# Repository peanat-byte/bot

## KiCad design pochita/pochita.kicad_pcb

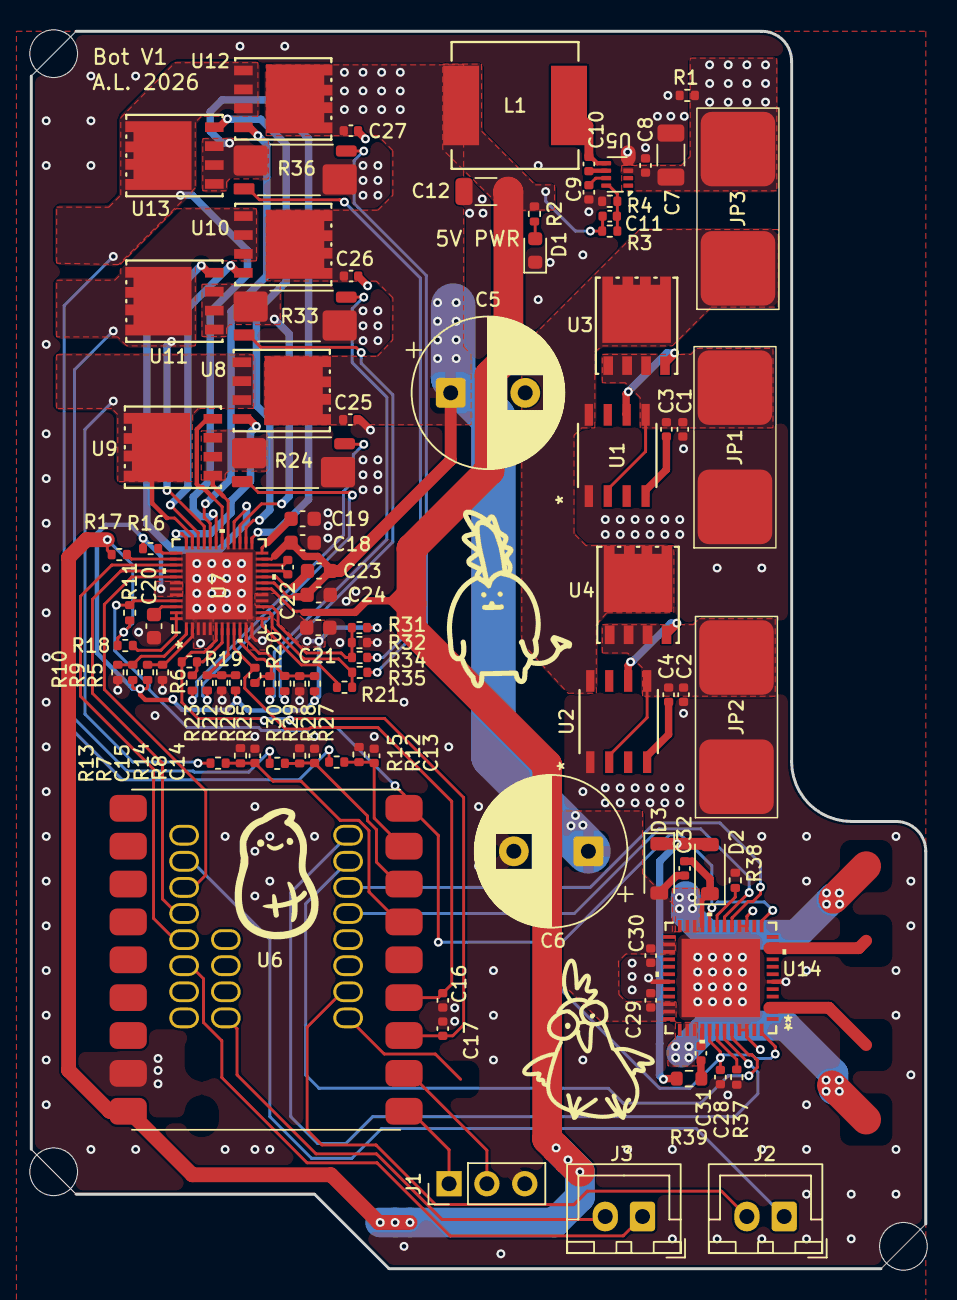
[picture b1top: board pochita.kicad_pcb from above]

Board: 4 copper layers, 60.0 x 83.0 mm, 98 parts (0 on the bottom side), 80 nets.

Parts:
C1, C2, C3, C4, C8, C9, C10, C11, C13, C14, C15, C16, C17, C22, C25, C26, C27, C28, C29, C30, C31, C32: C_0402_1005Metric
C5, C6: CP_Radial_D10.0mm_P5.00mm
C7, C12: C_1206_3216Metric
C18, C19, C20, C21, C23, C24: C_0603_1608Metric
D1: D_0603_1608Metric
D2, D3: D_SOD-123
H1, H2, H3: MountingHole_3.2mm_M3
J1: PinHeader_1x03_P2.54mm_Vertical
J2, J3: JST_XH_B2B-XH-A_1x02_P2.50mm_Vertical
JP1, JP2, JP3: 2-Pad
L1: IND_IHLP-3232DZ_VIS
R1, R2, R3, R4, R5, R6, R7, R8, R9, R10, R11, R12, R13, R14, R15, R16, R17, R18, R19, R20, R21, R22, R23, R25, R26, R27, R28, R29, R30, R31, R32, R34, R35, R37, R38: R_0402_1005Metric
R24, R33, R36: R_Shunt_Vishay_WSK2512_6332Metric_T1.19mm
R39: R_0603_1608Metric
U1, U2: SOIC8_D_TEX
U3, U4, U8, U9, U10, U11, U12, U13: SON_STL160N4F7_STM
U5: SOT-583-8
U6: ESP32-S3_Super_Mini
U7: VFQFPN48_ 6X6X1_STM
U14: VFQFPN48_7P15X7P15X0P5_STM

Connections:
+5V: C11.1, C12.1, L1.2, R2.1, R3.1, R11.1, R17.1, R18.1, U6.18 (5V), U7.18 (REGIN_3V3)
/Blade Motor/I1: C17.1, R19.1, U6.3 (GP1), U7.6 (OA_O1)
/Blade Motor/I2: C16.1, R20.1, U6.4 (GP2), U7.9 (OA_O2)
/Blade Motor/I3: R21.1, U7.13 (OA_O3)
/Blade Motor/IN1: U6.21 (GP16), U7.41 (INH1/IN1)
/Blade Motor/IN1N: R19.2, R23.1, U7.7 (OA_IN1N)
/Blade Motor/IN1P: R22.1, R25.1, R26.2, U7.8 (OA_IN1P)
/Blade Motor/IN2: U6.22 (GP17), U7.40 (INH2/IN2)
/Blade Motor/IN2N: R20.2, R30.1, U7.10 (OA_IN2N)
/Blade Motor/IN2P: R27.1, R28.2, R29.1, U7.11 (OA_IN2P)
/Blade Motor/IN3: U6.23 (GP18), U7.39 (INH3/IN3)
/Blade Motor/IN3N: R21.2, R35.1, U7.14 (OA_IN3N)
/Blade Motor/IN3P: R31.1, R32.2, R34.1, U7.15 (OA_IN3P)
/Blade Motor/V1: C15.1, R7.2, R13.1, U6.6 (GP4)
/Blade Motor/V2: C14.1, R8.2, R14.1, U6.7 (GP5)
/Blade Motor/V3: C13.1, R12.2, R15.1, U6.8 (GP6)
/Blade Motor/blade_motor_A: R13.2, U7.35 (OUT1), U8.1 (S), U8.2 (S), U8.3 (S), U9.5 (D)
/Blade Motor/blade_motor_B: R14.2, U7.33 (OUT2), U10.1 (S), U10.2 (S), U10.3 (S), U11.5 (D)
/Blade Motor/blade_motor_C: R15.2, U7.31 (OUT3), U12.1 (S), U12.2 (S), U12.3 (S), U13.5 (D)
/Blade Motor/nRST: C28.1, R11.2, U6.9 (GP7), U7.45 (NSTBY), U14.13 (OCDB), U14.20 (ENB), U14.41 (ENA), U14.48 (OCDA)
/Drive Motors/INA1: U6.31 (GP39), U14.43 (IN1A)
/Drive Motors/INA2: U6.32 (GP40), U14.44 (IN2A)
/Drive Motors/INB1: U6.33 (GP41), U14.17 (IN1B)
/Drive Motors/INB2: U6.34 (GP42), U14.18 (IN2B)
/Drive Motors/drive_motor_A1: U14.2 (OUT1A), U14.3 (OUT1A)
/Drive Motors/drive_motor_A2: U14.38 (OUT2A), U14.39 (OUT2A)
/Drive Motors/drive_motor_B1: U14.10 (OUT1B), U14.11 (OUT1B)
/Drive Motors/drive_motor_B2: U14.22 (OUT2B), U14.23 (OUT2B)
GND: C1.2, C2.2, C5.2, C6.2, C7.2, C8.2, C9.2, C12.2, C13.2, C14.2, C15.2, C16.2, C17.2, C18.2, C19.2, C20.2, C21.2, C24.2, C25.2, C26.2, C27.2, C28.2, C29.2, C30.2, D1.1 (K), J1.3, JP1.1 (A), JP2.1 (A), R1.2, R4.2, R6.2, R7.1, R8.1, R10.2, R12.1, R24.4, R26.1, R28.1, R32.1, R33.4, R36.4, R37.2, R38.2, U1.1 (GND), U2.1 (GND), U5.4 (GND), U6.17 (GND), U7.3 (C_IN1), U7.4 (C_IN2), U7.5 (C_IN3), U7.12 (AGND), U7.49 (EPAD), U14.6 (GND), U14.15 (SENSEB), U14.16 (SENSEB), U14.31 (GND), U14.45 (SENSEA), U14.46 (SENSEA), U14.49 (EPAD)
unnamed: C31.2, R39.1
unnamed: D1.2 (A), R2.2
unnamed: D2.1 (K), D3.2 (A), R39.2
unnamed: C32.2, D3.1 (K), U14.21 (VBOOT)
unnamed: J1.1, U6.1 (TX)
unnamed: J1.2, U6.2 (RX)
unnamed: J2.1, U6.20 (GP15)
unnamed: J2.2, U6.37 (GP47)
unnamed: J3.1, U6.24 (GP21)
unnamed: J3.2, U6.30 (GP38)
unnamed: JP3.1 (A), U1.8 (CATHODE), U2.8 (CATHODE), U3.5 (D), U4.5 (D)
unnamed: R22.2, R24.2
unnamed: R23.2, R24.3
unnamed: R29.2, R33.2
unnamed: R30.2, R33.3
unnamed: R34.2, R36.2
unnamed: R35.2, R36.3
unnamed: U1.6 (GATE), U3.4 (G)
unnamed: C3.2, U1.4 (VCAP)
unnamed: U2.6 (GATE), U4.4 (G)
unnamed: C4.2, U2.4 (VCAP)
unnamed: C10.1, U5.6 (BST)
unnamed: C11.2, R3.2, R4.1, U5.8 (FB)
unnamed: C9.1, U5.7 (SS)
unnamed: C10.2, L1.1, U5.5 (SW)
unnamed: R18.2, U7.47 (EN), U7.48 (NFAULT)
unnamed: R16.2, U7.37 (FLAG)
unnamed: U7.36 (GHS1), U8.4 (G)
unnamed: U7.30 (GLS1), U9.4 (G)
unnamed: R5.2, R6.1, U7.2 (IGATE)
unnamed: C20.1, U7.46 (LGC_CAP)
unnamed: C22.1, U7.22 (NCAP)
unnamed: C22.2, U7.21 (PCAP)
unnamed: R24.1, U7.29 (SLS1), U9.1 (S), U9.2 (S), U9.3 (S)
unnamed: R33.1, U7.27 (SLS2), U11.1 (S), U11.2 (S), U11.3 (S)
unnamed: R36.1, U7.25 (SLS3), U13.1 (S), U13.2 (S), U13.3 (S)
unnamed: R9.2, R10.1, U7.1 (TCC)
unnamed: C23.1, U7.20 (VBOOT)
unnamed: C19.1, U7.24 (VCC)
unnamed: R17.2, U7.38 (VDSTH)
unnamed: U7.34 (GHS2), U10.4 (G)
unnamed: U7.28 (GLS2), U11.4 (G)
unnamed: U7.32 (GHS3), U12.4 (G)
unnamed: U7.26 (GLS3), U13.4 (G)
unnamed: R37.1, U14.42 (PROGCLA)
unnamed: R38.1, U14.19 (PROGCLB)
unnamed: C31.1, U14.40 (VCP)
VBAT: C1.1, C3.1, JP1.2 (B), U1.2 (EN), U1.5 (ANODE), U3.1 (S), U3.2 (S), U3.3 (S)
VBAT_BACKUP: C2.1, C4.1, JP2.2 (B), U2.2 (EN), U2.5 (ANODE), U4.1 (S), U4.2 (S), U4.3 (S)
VBUS: C5.1, C6.1, C7.1, C8.1, C18.1, C23.2, C24.1, C25.1, C26.1, C27.1, C29.1, C30.1, C32.1, D2.2 (A), JP3.2 (B), R1.1, U5.3 (VIN), U7.19 (VM), U7.23 (VS), U8.5 (D), U10.5 (D), U12.5 (D), U14.26 (VSB), U14.27 (VSB), U14.34 (VSA), U14.35 (VSA)
VDD: C21.1, R5.1, R9.1, R16.1, R25.2, R27.2, R31.2, U7.16 (CREF), U7.17 (VDD), U7.42 (INL3/EN3), U7.43 (INL2/EN2), U7.44 (INL1/EN1)

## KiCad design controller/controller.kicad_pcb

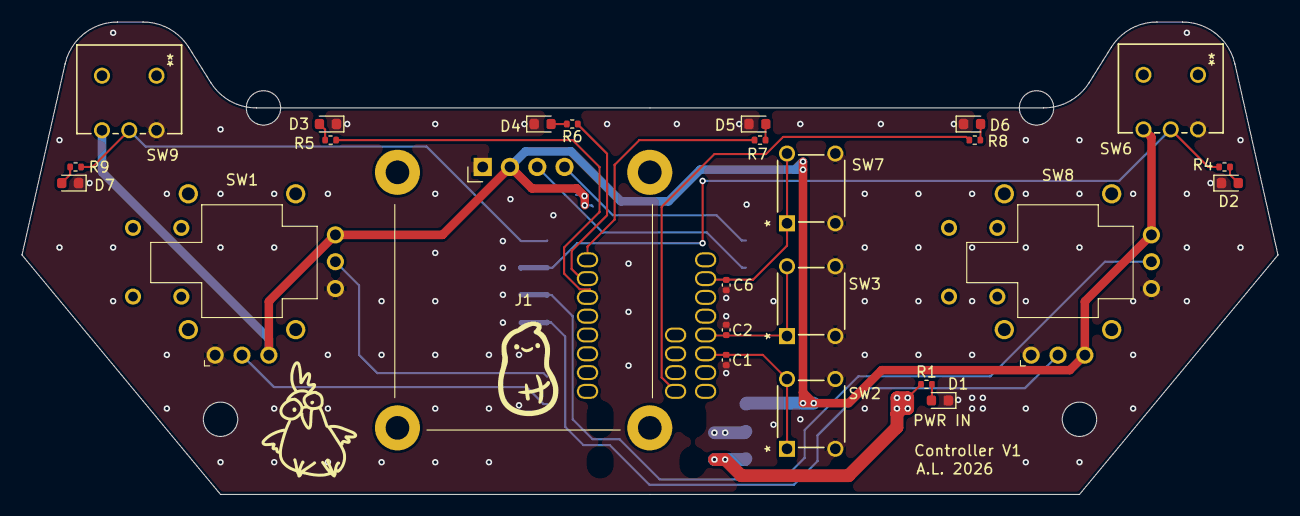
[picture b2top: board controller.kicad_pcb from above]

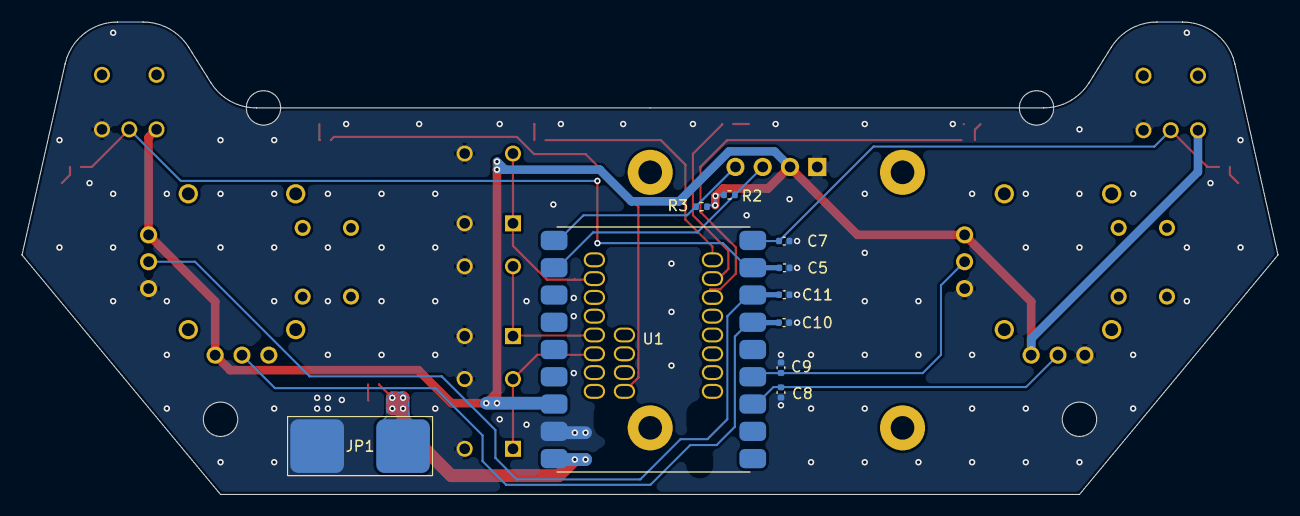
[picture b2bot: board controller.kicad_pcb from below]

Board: 4 copper layers, 117.0 x 44.0 mm, 39 parts (10 on the bottom side), 25 nets.

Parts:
C1, C2, C5, C6, C7, C8, C9, C10, C11: C_0402_1005Metric
D1, D2, D3, D4, D5, D6, D7: D_0603_1608Metric
H1, H2, H4: MountingHole_3.2mm_M3
H3: MountingHole; MountingHole_3.2mm_M3
J1: LCD_Screen_Module
JP1: 2-Pad
R1, R2, R3, R4, R5, R6, R7, R8, R9: R_0402_1005Metric
SW1, SW8: PS5 TMR Joystick; PS5_TMR_Joystick
SW2, SW3, SW7: SW4_1825910-B_TEC
SW6, SW9: SW_SPDT; SPDT05_ATE1D_9P5X8_NDC
U1: ESP32-S3_Super_Mini

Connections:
3V3: J1.2, R2.1, R3.1, SW1.3 (VCC), SW1.6 (VCC), SW6.1 (A), SW8.3 (VCC), SW8.6 (VCC), SW9.1 (A), U1.16 (3V3)
/SCL: J1.3, R2.2, U1.11 (GP9)
/SDA: J1.4, R3.2, U1.10 (GP8)
GND: C1.2, C2.2, C5.2, C6.2, C7.2, C8.2, C9.2, C10.2, C11.2, D1.1 (K), D2.1 (K), D3.1 (K), D4.1 (K), D5.1 (K), D6.1 (K), D7.1 (K), J1.1, JP1.1 (A), SW1.1 (GND), SW1.4 (GND), SW2.3 (K), SW2.4 (A), SW3.3 (K), SW3.4 (A), SW6.3 (C), SW7.3 (K), SW7.4 (A), SW8.1 (GND), SW8.4 (GND), SW9.3 (C), U1.17 (GND)
unnamed: D1.2 (A), R1.2
unnamed: D2.2 (A), R4.2
unnamed: D3.2 (A), R5.2
unnamed: D4.2 (A), R6.2
unnamed: D5.2 (A), R7.2
unnamed: D6.2 (A), R8.2
unnamed: D7.2 (A), R9.2
unnamed: C8.1, SW1.2 (OUT1), U1.3 (GP1)
unnamed: C9.1, SW1.5 (OUT2), U1.4 (GP2)
unnamed: C5.1, R4.1, SW6.2 (B), U1.8 (GP6)
unnamed: C10.1, SW8.2 (OUT1), U1.6 (GP4)
unnamed: C11.1, SW8.5 (OUT2), U1.7 (GP5)
unnamed: C7.1, R9.1, SW9.2 (B), U1.9 (GP7)
unnamed: C6.1, SW7.1, SW7.2, U1.20 (GP15)
unnamed: C2.1, SW3.1, SW3.2, U1.23 (GP18)
unnamed: C1.1, SW2.1, SW2.2, U1.24 (GP21)
unnamed: R8.1, U1.30 (GP38)
unnamed: R7.1, U1.31 (GP39)
unnamed: R6.1, U1.32 (GP40)
unnamed: R5.1, U1.33 (GP41)
VCC: JP1.2 (B), R1.1, U1.18 (5V)
